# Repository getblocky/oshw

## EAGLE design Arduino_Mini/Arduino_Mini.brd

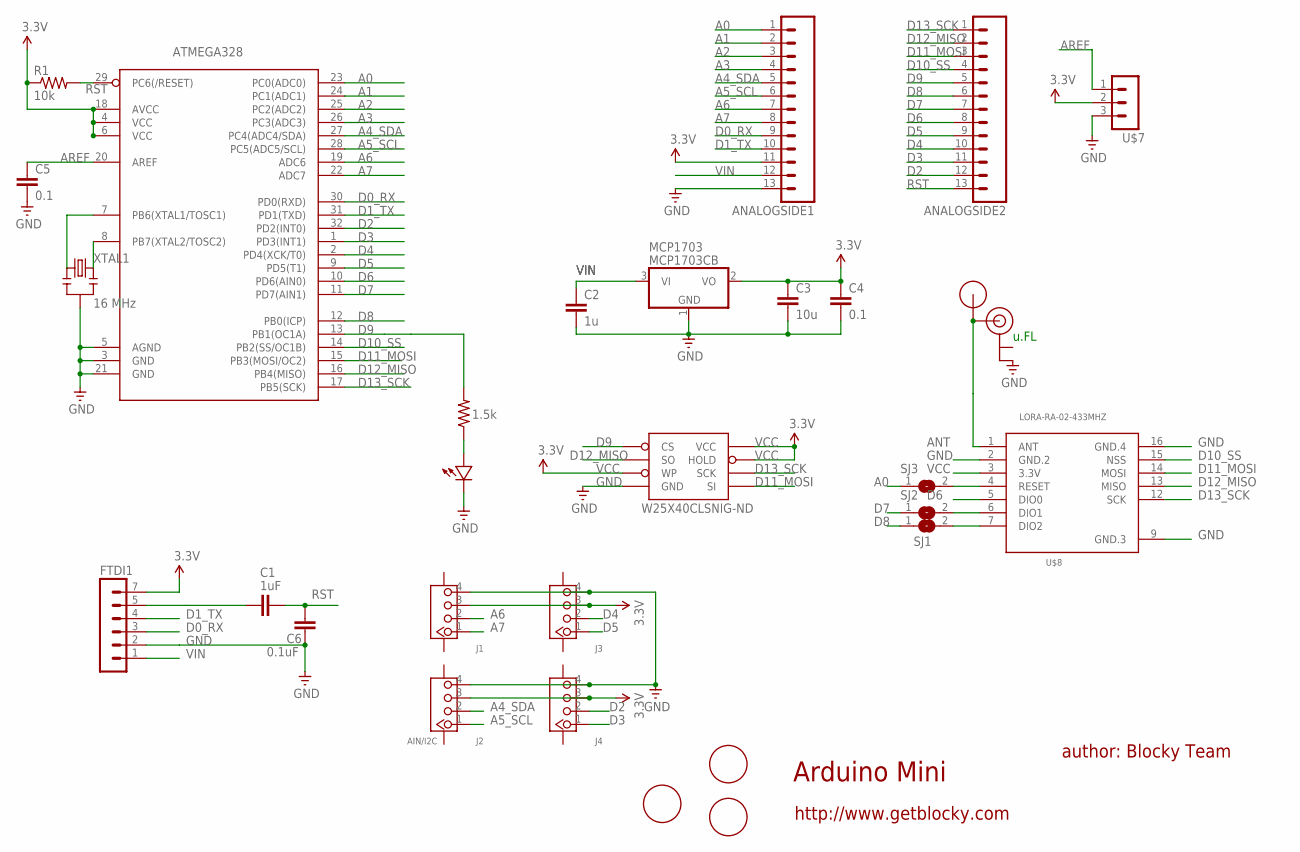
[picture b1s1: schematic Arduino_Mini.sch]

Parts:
ANALOGSIDE1, ANALOGSIDE2: HDR_13PINTHIN_RINGS; 1X13_THINRINGS
ATMEGA328: ATMega-328; TQFP32-08
C1: 1uF; 0603-CAP
C2: 1u; 0603-CAP
C3: 10u; 0805-CAP
C4, C5: 0.1; 0603-CAP
C6: 0.1uF; 0603-CAP
FTDI1: HDR_6PINTHINRINGS; 1X06_NS_THINRINGS
J1, J3, J4: 4P-SMD-2.0-90D; HW4-SMD-2.0-90D
J2: AIN/I2C; HW4-SMD-2.0-90D
LED: LED0603; 0603-LED
MCP1703: MCP1703CB; SOT23
R1: 10k; 0603-RES
R2: 1.5k; 0603-RES
SJ1, SJ2, SJ3: SOLDERJUMPERREFLOW; SOLDERJUMPER_REFLOW
U$1: RFM12B_ANTENNA""; RFM12B-ANTENNA
U$2, U$5, U$6: FIDUCIAL1.5MM; FIDUCIAL_1.5MM
U$4: U.FL
U$7: HDR_3PINTHINRINGS; 1X03_NS_THINRINGS
U$8: LORA-RA-02-433MHZ; LORA-RA2-SMD
W25X40CLSNIG-ND: AT25F512BJEDEC_3.9MM; SO08
XTAL1: 16 MHz; RESONATOR-SMD

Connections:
A0: ANALOGSIDE1.1, ATMEGA328.23 (PC0(ADC0)), SJ3.1
A1: ANALOGSIDE1.2, ATMEGA328.24 (PC1(ADC1))
A2: ANALOGSIDE1.3, ATMEGA328.25 (PC2(ADC2))
A3: ANALOGSIDE1.4, ATMEGA328.26 (PC3(ADC3))
A4_SDA: ANALOGSIDE1.5, ATMEGA328.27 (PC4(ADC4/SDA)), J2.2
A5_SCL: ANALOGSIDE1.6, ATMEGA328.28 (PC5(ADC5/SCL)), J2.1
A6: ANALOGSIDE1.7, ATMEGA328.19 (ADC6), J1.2
A7: ANALOGSIDE1.8, ATMEGA328.22 (ADC7), J1.1
ANT: U$1.P$1, U$4.SIGNAL, U$8.1 (ANT)
AREF: ATMEGA328.20 (AREF), C5.1, U$7.1
D0_RX: ANALOGSIDE1.9, ATMEGA328.30 (PD0(RXD)), FTDI1.3
D1_TX: ANALOGSIDE1.10, ATMEGA328.31 (PD1(TXD)), FTDI1.4
D2: ANALOGSIDE2.12, ATMEGA328.32 (PD2(INT0)), J4.2
D3: ANALOGSIDE2.11, ATMEGA328.1 (PD3(INT1)), J4.1
D4: ANALOGSIDE2.10, ATMEGA328.2 (PD4(XCK/T0)), J3.2
D5: ANALOGSIDE2.9, ATMEGA328.9 (PD5(T1)), J3.1
D6: ANALOGSIDE2.8, ATMEGA328.10 (PD6(AIN0)), U$8.5 (DIO0)
D7: ANALOGSIDE2.7, ATMEGA328.11 (PD7(AIN1)), SJ2.1
D8: ANALOGSIDE2.6, ATMEGA328.12 (PB0(ICP)), SJ1.1
D9: ANALOGSIDE2.5, ATMEGA328.13 (PB1(OC1A)), R2.2, W25X40CLSNIG-ND.1_CS (CS)
D10_SS: ANALOGSIDE2.4, ATMEGA328.14 (PB2(SS/OC1B)), U$8.15 (NSS)
D11_MOSI: ANALOGSIDE2.3, ATMEGA328.15 (PB3(MOSI/OC2)), U$8.14 (MOSI), W25X40CLSNIG-ND.5_SI (SI)
D12_MISO: ANALOGSIDE2.2, ATMEGA328.16 (PB4(MISO)), U$8.13 (MISO), W25X40CLSNIG-ND.2_SO (SO)
D13_SCK: ANALOGSIDE2.1, ATMEGA328.17 (PB5(SCK)), U$8.12 (SCK), W25X40CLSNIG-ND.6_SCK (SCK)
DIO1: SJ2.2, U$8.6 (DIO1)
DIO2: SJ1.2, U$8.7 (DIO2)
GND: ANALOGSIDE1.13, ATMEGA328.3 (GND), ATMEGA328.5 (AGND), ATMEGA328.21 (GND), C2.2, C3.2, C4.2, C5.2, C6.2, FTDI1.2, J1.4, J2.4, J3.4, J4.4, LED.MINUS, MCP1703.1 (GND), U$4.GND2 (GND), U$7.3, U$8.2 (GND.2), U$8.9 (GND.3), U$8.16 (GND.4), W25X40CLSNIG-ND.4_GND (GND), XTAL1.2
unnamed: ATMEGA328.7 (PB6(XTAL1/TOSC1)), XTAL1.1
unnamed: LED.PLUS, R2.1
unnamed: SJ3.2, U$8.4 (RESET)
unnamed: C1.2, FTDI1.5
unnamed: ATMEGA328.8 (PB7(XTAL2/TOSC2)), XTAL1.3
RST: ANALOGSIDE2.13, ATMEGA328.29 (PC6(/RESET)), C1.1, C6.1, R1.2
VCC: ANALOGSIDE1.11, ATMEGA328.4 (VCC), ATMEGA328.6 (VCC), ATMEGA328.18 (AVCC), C3.1, C4.1, FTDI1.7 (6), J1.3, J2.3, J3.3, J4.3, MCP1703.2 (VO), R1.1, U$7.2, U$8.3 (3.3V), W25X40CLSNIG-ND.3_WP (WP), W25X40CLSNIG-ND.7_HOLD (HOLD), W25X40CLSNIG-ND.8_VCC (VCC)
VIN: ANALOGSIDE1.12, C2.1, FTDI1.1, MCP1703.3 (VI)

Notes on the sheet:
Arduino Mini
author: Blocky Team
http://www.getblocky.com
u.FL

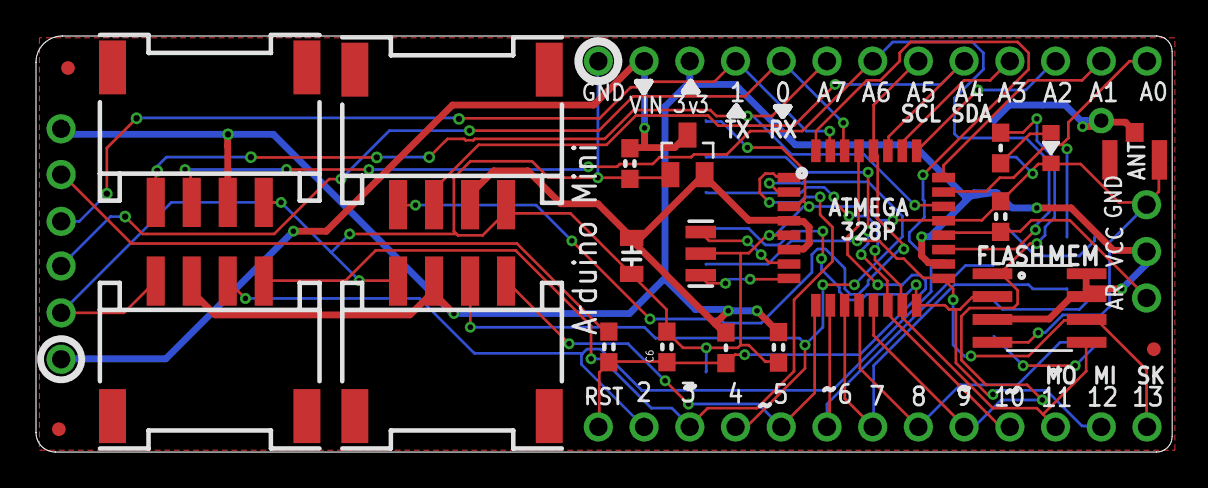
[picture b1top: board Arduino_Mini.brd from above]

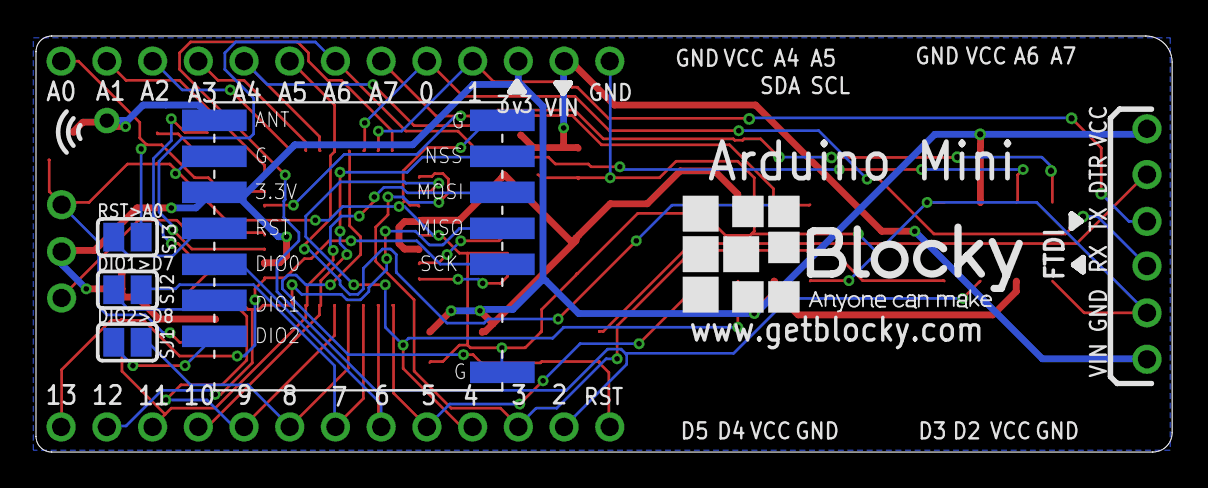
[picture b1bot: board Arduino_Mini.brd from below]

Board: 2 copper layers, 63.1 x 23.1 mm, 31 parts (5 on the bottom side), 35 nets.

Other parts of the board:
U$3: BLOCKY_LOGO

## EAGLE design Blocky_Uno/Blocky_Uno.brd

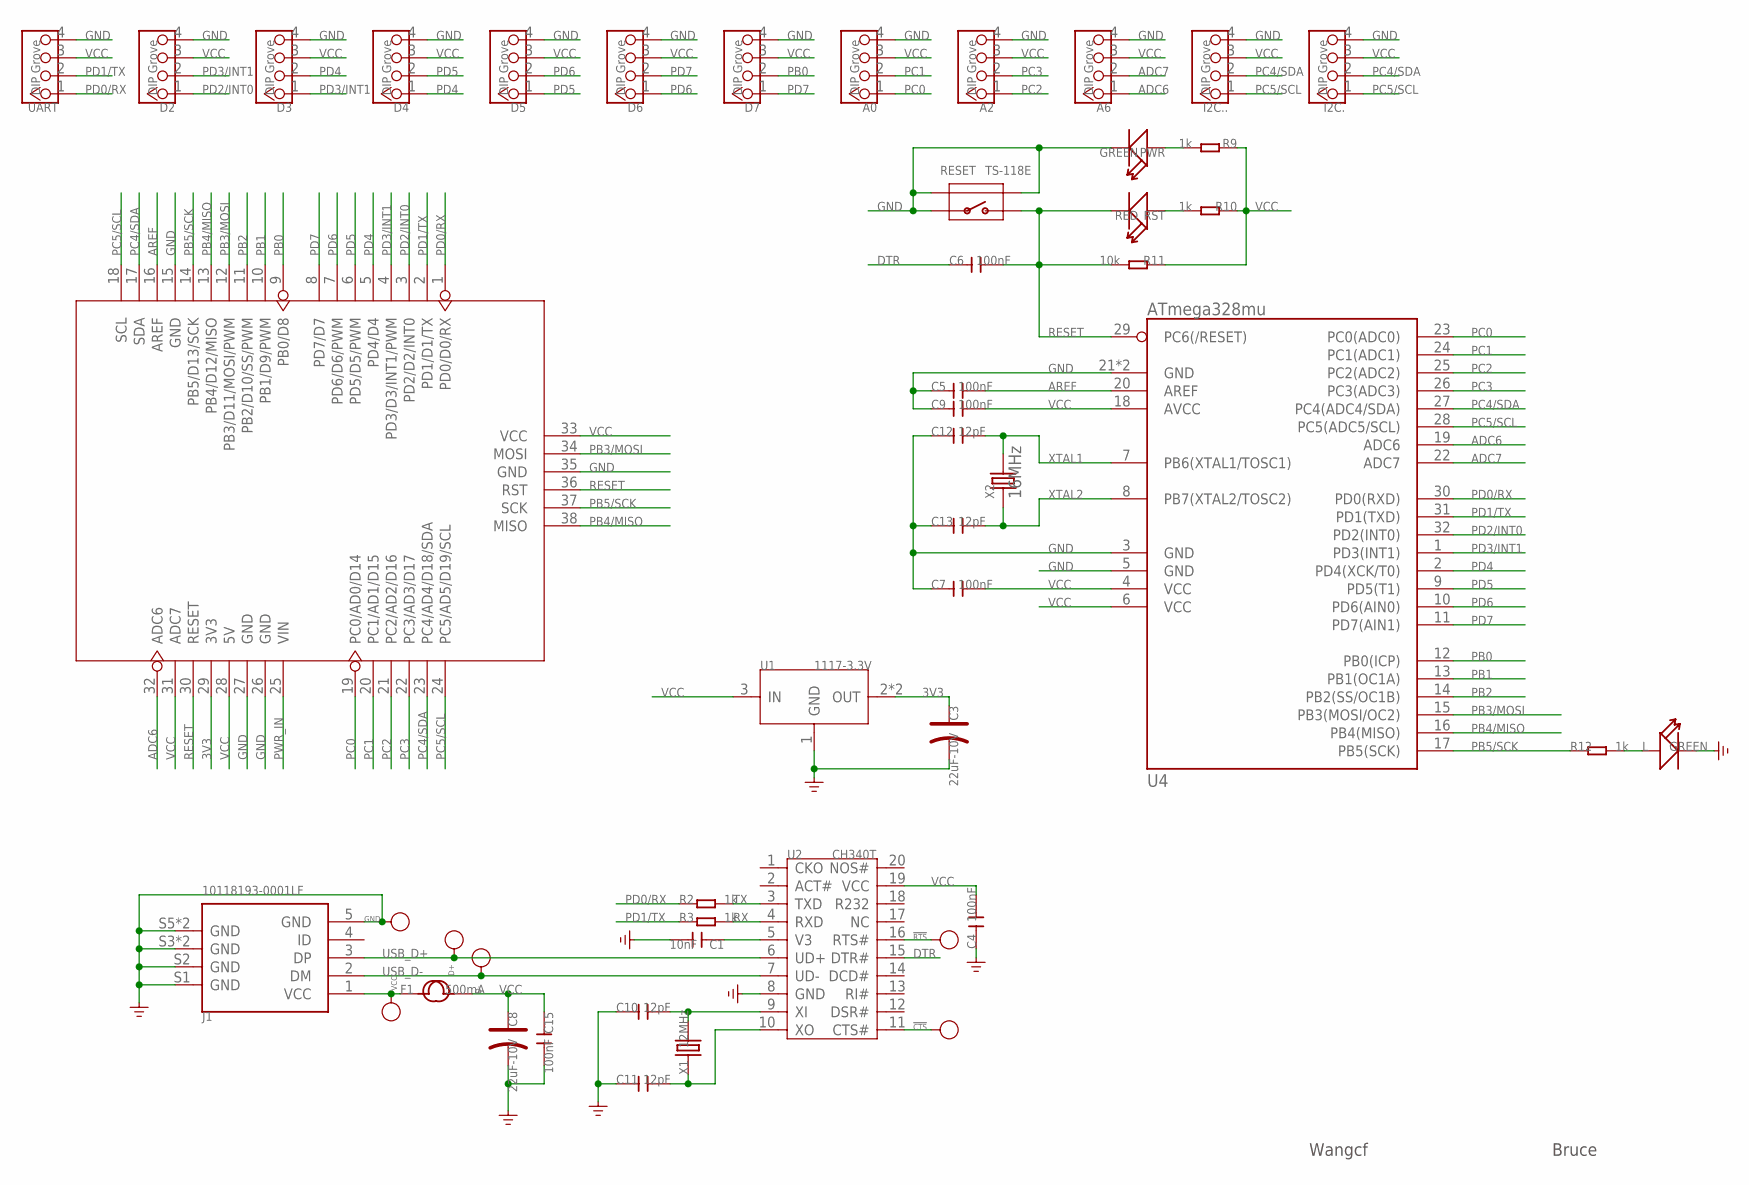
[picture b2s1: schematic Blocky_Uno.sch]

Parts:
!CTS: PAD-TEST-POINT'4545'; TP_4545
!RTS: PAD-TEST-POINT'4545'; TP_4545
A0, A2, A6: DIP Grove; 4P-2.0
C1: 10nF; C0603
C3, C8: 22uF-10V; AVX-A
C4, C5, C6, C7, C9, C15: 100nF; C0603
C10, C11, C12, C13: 12pF; C0603
D2, D3, D4, D5, D6, D7: DIP Grove; 4P-2.0
D+: PAD-TEST-POINT'4545'; TP_4545
D-: PAD-TEST-POINT'4545'; TP_4545
F1: 500mA; F1206
GND: PAD-TEST-POINT'4545'; TP_4545
I2C., I2C..: DIP Grove; 4P-2.0
J1: 10118193-0001LF; MICRO-USB5+6P-SMD-0.65-B
L: GREEN; LED-0603
PWR: GREEN; LED-0603
R2, R3, R9, R10, R12: 1k; R0603
R11: 10k; R0603
RESET: TS-118E; 4P-SMD-7X3.5X3.5H
RST: RED; LED-0603
U1: 1117-3.3V; SOT89
U2: CH340T; SSOP20
U3: ARDUINO-38P
U4: ATmega328mu; MLF32X-W/HEAT
UART: DIP Grove; 4P-2.0
VCC: PAD-TEST-POINT'4545'; TP_4545
X1: 12MHz; 2P-SMD-5X3.2
X2: 16MHz; 2P-SMD-5X3.2

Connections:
3V3: C3.+, U1.2 (OUT), U1.4 (OUT), U3.29 (3V3)
ADC6: A6.1, U3.32 (ADC6), U4.19 (ADC6)
ADC7: A6.2, U4.22 (ADC7)
AREF: C5.2, U3.16 (AREF), U4.20 (AREF)
CTS: !CTS.T, U2.11 (CTS#)
DTR: C6.1, U2.15 (DTR#)
GND: A0.4, A2.4, A6.4, C1.2, C3.-, C4.1, C5.1, C7.1, C8.-, C9.1, C10.1, C11.1, C12.1, C13.1, C15.2, D2.4, D3.4, D4.4, D5.4, D6.4, D7.4, GND.T, I2C..4, I2C...4, J1.5 (GND), J1.S1 (GND), J1.S2 (GND), J1.S3 (GND), J1.S4 (GND), J1.S5 (GND), J1.S6 (GND), L.-, PWR.-, RESET.1, RESET.S1, RESET.S2, U1.1 (GND), U2.8 (GND), U3.15 (GND), U3.26 (GND), U3.27 (GND), U3.35 (GND), U4.3 (GND), U4.5 (GND), U4.21 (GND), U4.HEAT (GND), UART.4
unnamed: R10.2, RST.+
unnamed: PWR.+, R9.2
unnamed: C10.2, U2.9 (XI), X1.2
unnamed: C11.2, U2.10 (XO), X1.1
unnamed: !RTS.T, U2.16 (RTS#)
unnamed: F1.1, J1.1 (VCC), VCC.T
unnamed: L.+, R12.2
PB0: D7.2, U3.9 (PB0/D8), U4.12 (PB0(ICP))
PB1: U3.10 (PB1/D9/PWM), U4.13 (PB1(OC1A))
PB2: U3.11 (PB2/D10/SS/PWM), U4.14 (PB2(SS/OC1B))
PB3/MOSI: U3.12 (PB3/D11/MOSI/PWM), U3.34 (MOSI), U4.15 (PB3(MOSI/OC2))
PB4/MISO: U3.13 (PB4/D12/MISO), U3.38 (MISO), U4.16 (PB4(MISO))
PB5/SCK: R12.1, U3.14 (PB5/D13/SCK), U3.37 (SCK), U4.17 (PB5(SCK))
PC0: A0.1, U3.19 (PC0/AD0/D14), U4.23 (PC0(ADC0))
PC1: A0.2, U3.20 (PC1/AD1/D15), U4.24 (PC1(ADC1))
PC2: A2.1, U3.21 (PC2/AD2/D16), U4.25 (PC2(ADC2))
PC3: A2.2, U3.22 (PC3/AD3/D17), U4.26 (PC3(ADC3))
PC4/SDA: I2C..2, I2C...2, U3.17 (SDA), U3.23 (PC4/AD4/D18/SDA), U4.27 (PC4(ADC4/SDA))
PC5/SCL: I2C..1, I2C...1, U3.18 (SCL), U3.24 (PC5/AD5/D19/SCL), U4.28 (PC5(ADC5/SCL))
PD0/RX: R2.1, U3.1 (PD0/D0/RX), U4.30 (PD0(RXD)), UART.1
PD1/TX: R3.1, U3.2 (PD1/D1/TX), U4.31 (PD1(TXD)), UART.2
PD2/INT0: D2.1, U3.3 (PD2/D2/INT0), U4.32 (PD2(INT0))
PD3/INT1: D2.2, D3.1, U3.4 (PD3/D3/INT1/PWM), U4.1 (PD3(INT1))
PD4: D3.2, D4.1, U3.5 (PD4/D4), U4.2 (PD4(XCK/T0))
PD5: D4.2, D5.1, U3.6 (PD5/D5/PWM), U4.9 (PD5(T1))
PD6: D5.2, D6.1, U3.7 (PD6/D6/PWM), U4.10 (PD6(AIN0))
PD7: D6.2, D7.1, U3.8 (PD7/D7), U4.11 (PD7(AIN1))
PWR_IN: U3.25 (VIN)
RESET: C6.2, R11.2, RESET.2, RST.-, U3.30 (RESET), U3.36 (RST), U4.29 (PC6(/RESET))
RX: R3.2, U2.4 (RXD)
TX: R2.2, U2.3 (TXD)
USB_D+: D+.T, J1.3 (DP), U2.6 (UD+)
USB_D-: D-.T, J1.2 (DM), U2.7 (UD-)
V3: C1.1, U2.5 (V3)
VCC: A0.3, A2.3, A6.3, C4.2, C7.2, C8.+, C9.2, C15.1, D2.3, D3.3, D4.3, D5.3, D6.3, D7.3, F1.2, I2C..3, I2C...3, R9.1, R10.1, R11.1, U1.3 (IN), U2.19 (VCC), U3.28 (5V), U3.31 (ADC7), U3.33 (VCC), U4.4 (VCC), U4.6 (VCC), U4.18 (AVCC), UART.3
XTAL1: C12.2, U4.7 (PB6(XTAL1/TOSC1)), X2.2
XTAL2: C13.2, U4.8 (PB7(XTAL2/TOSC2)), X2.1

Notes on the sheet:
Wangcf
Bruce

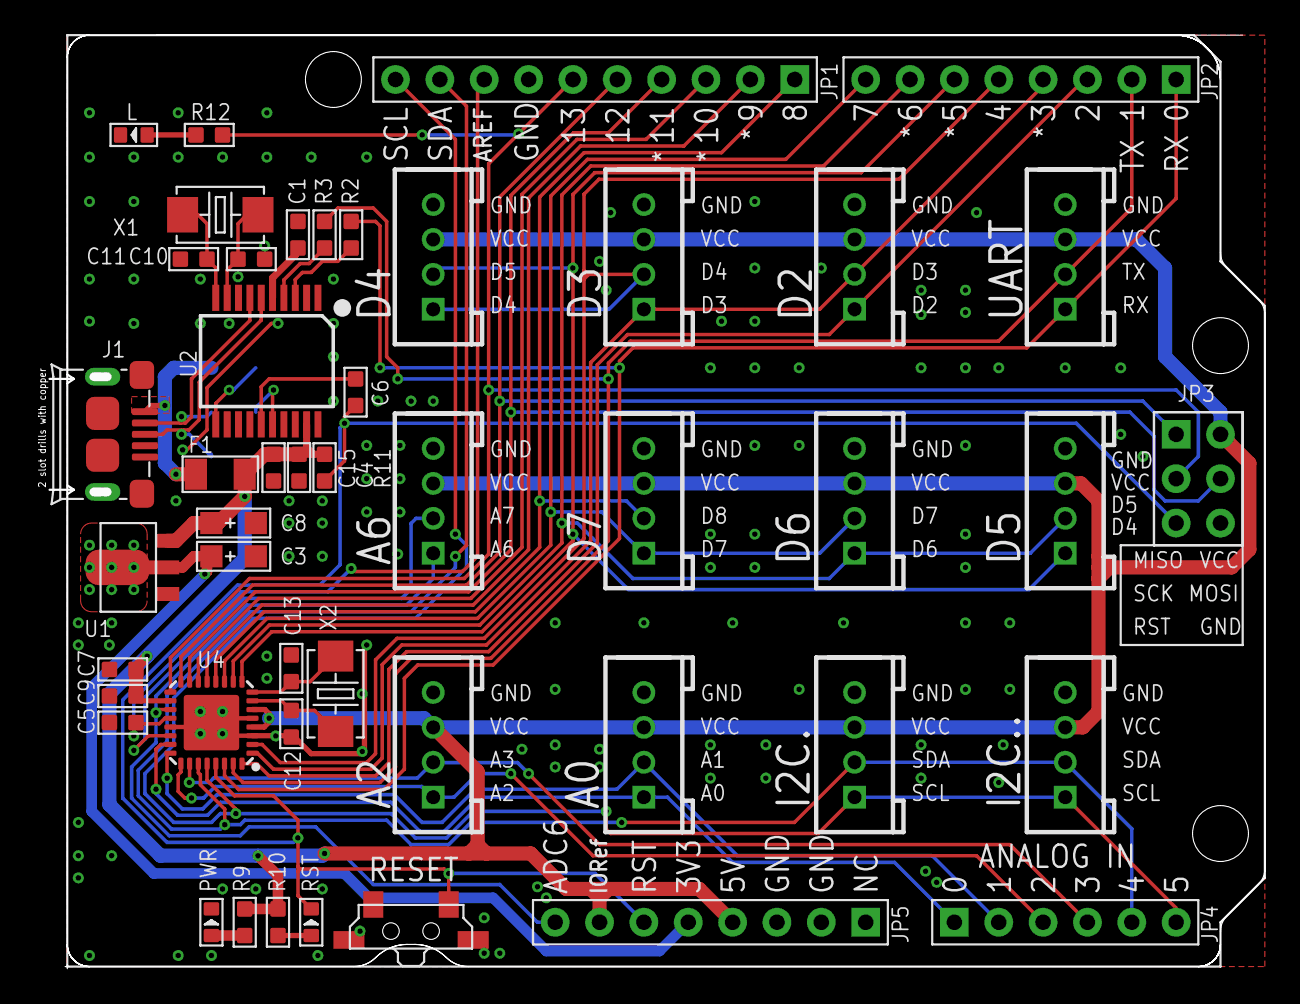
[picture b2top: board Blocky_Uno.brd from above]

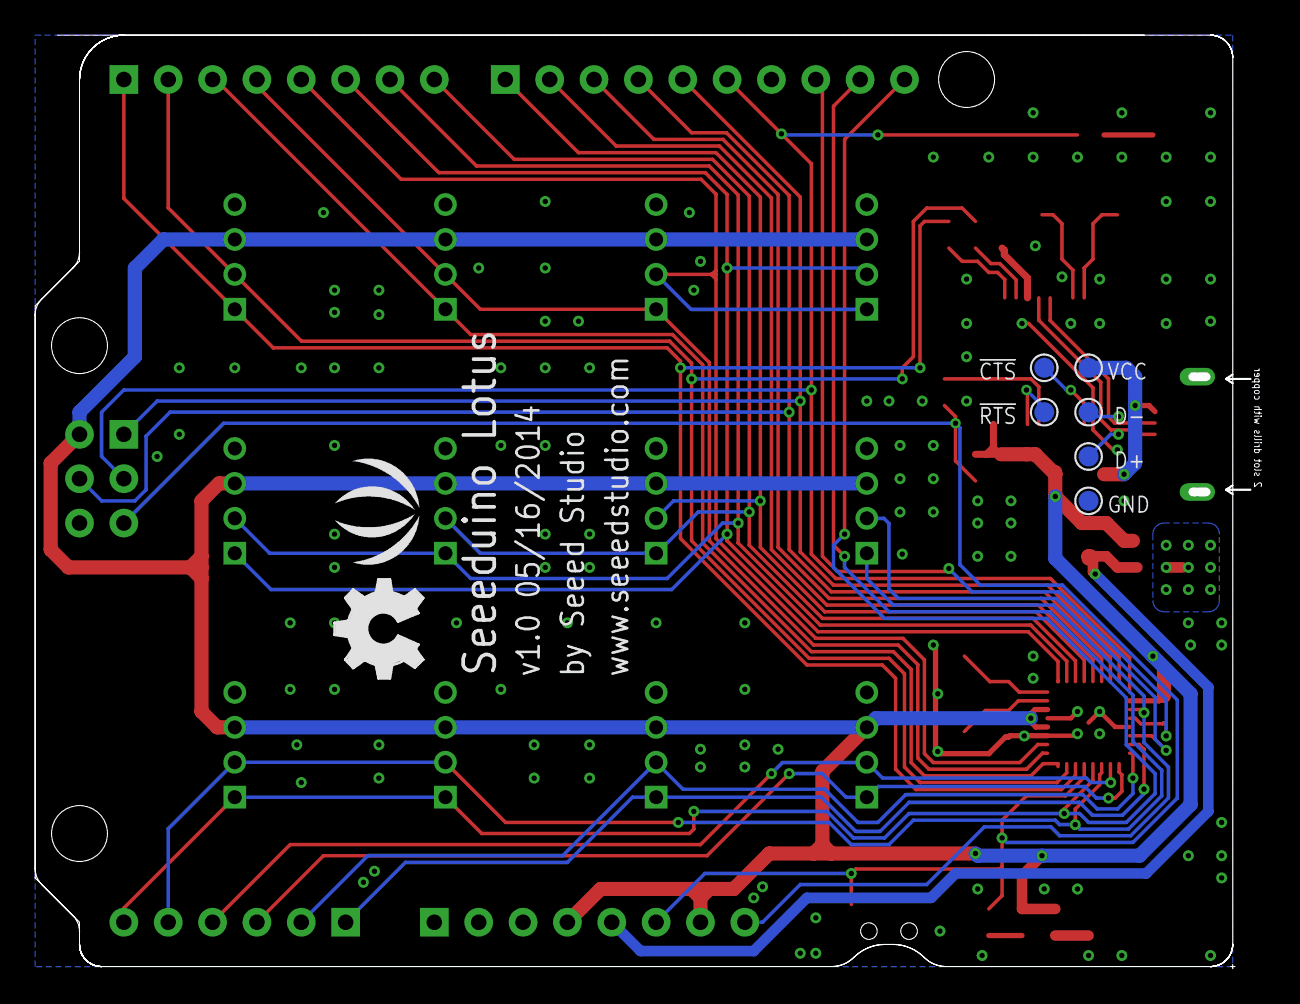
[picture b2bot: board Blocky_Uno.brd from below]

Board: 2 copper layers, 69.6 x 53.5 mm, 52 parts (8 on the bottom side), 43 nets.

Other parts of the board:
U$2: OSHW_FILLX200_NOTEXT
U$4: LOGO_SILK
U$12: SEEED_MASK

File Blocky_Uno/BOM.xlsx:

| Part | Package | Quantity | Link
 | DIP Grove | 4P-2.0 | 12
 | 10nF | C0603 | 1
 | Cap tantalum 3216 22uF 10V | AVX-A 3216 | 2 | https://www.aliexpress.com/item/Free-shipping-20pcs-A-3216-2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
 | 100nF | C0603 | 6
 | 12pF | C0603 | 4
 | Fuse 1206 500mA | F1206 | 1 | https://www.aliexpress.com/item/100PCS-1206-0-5A-0-5-Amp-500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
 | MICRO-B-SMD 10118193-0001LF | MICRO-USB | 1 | https://www.digikey.com/product-detail/en/amphenol-fci/10118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
 | LED GREEN | LED-0603 | 2
 | Resistor 1k | R0603 | 5
 | Resistor 10k | R0603 | 1
 | Side SMD Tact Switch 3.5x7.0x3.5 TS-118E | 4P-SMD-7X3.5X3.5H | 1 | https://www.aliexpress.com/item/1000pcs-on-tape-reel-Horizon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
 | LED RED | LED-0603 | 1
 | LDO AMS1117-3.3V SOT89 | SOT89 | 1 | https://www.aliexpress.com/item/100PCS-AMS1117-3-3V-AMS1117-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
 | CH340T | SSOP20 | 1 | https://www.aliexpress.com/item/Smd-CH340T-wch-usb-to-serial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
 | Atmega328p-mu | MLF32X-W/HEAT | 1 | https://www.aliexpress.com/item/Free-Shipping-ATMEGA328P-MUR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
 | Crystal SMD 5032 12MHz | 2P-SMD-5X3.2 | 1 | https://www.aliexpress.com/item/NDK-NX5032GA-NX5032GB-12M-12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
 | Crystal SMD 5032 16MHz | 2P-SMD-5X3.2 | 1 | Crystal SMD 16MHz 5032 https://www.aliexpress.com/item/20PCS-16MHZ-5032-SMD-Pas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

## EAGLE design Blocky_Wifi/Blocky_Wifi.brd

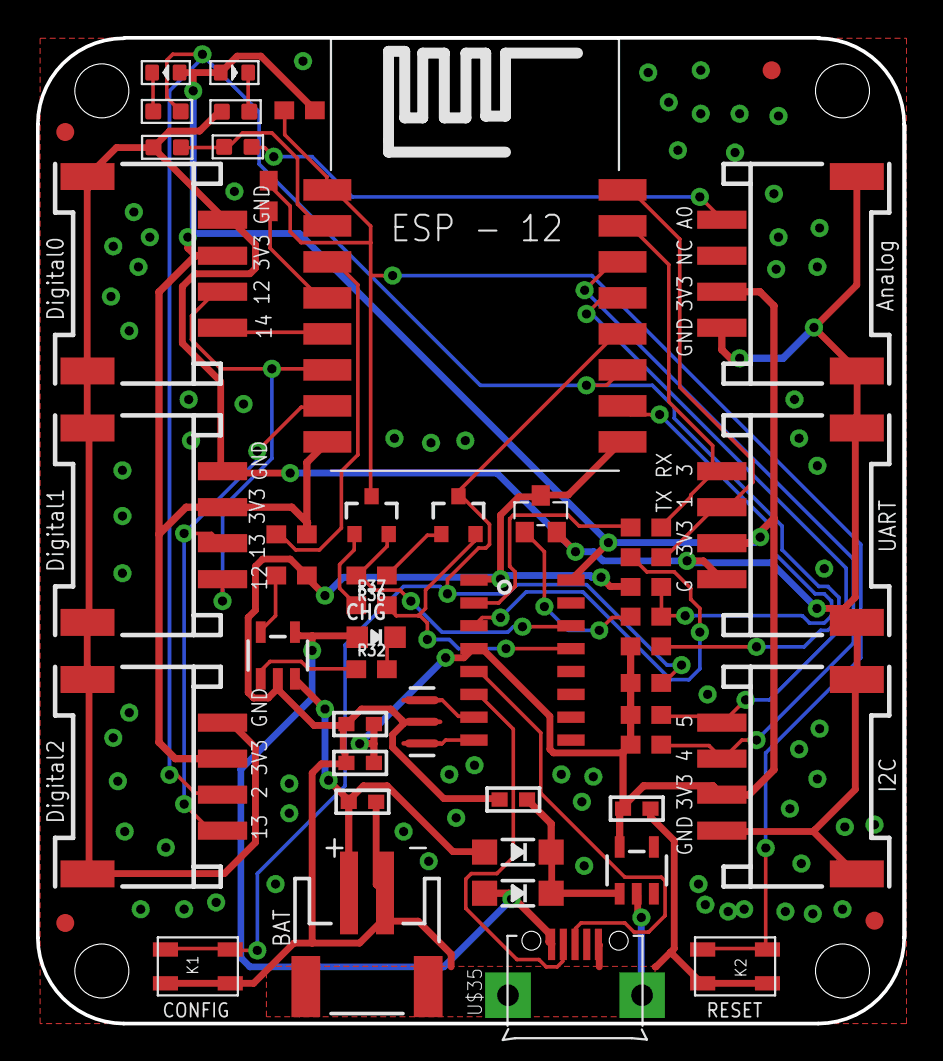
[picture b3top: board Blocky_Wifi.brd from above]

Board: 2 copper layers, 48.1 x 54.8 mm, 52 parts (1 on the bottom side), 37 nets.

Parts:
C1: 1uF; _0603
C3, C6, C10: 10uF; _0603
C11: 0.1uF; _0603
CHG: CHARGE; CHIPLED_0805_NOOUTLINE
D4: Blue; LED-0603
D5: Red; LED-0603
D6, D7: MBR120; SOD-123
J3, J4, J5, J6, J7, J8: DIP Grove; HW4-SMD-2.0-90D
J9: JST-2-SMD
K1, K2: button 311020045; SW4P-SMD-4.5X3.2X2.5MM
Q3, Q6: S8050; SOT23-3
Q7: S8050; SOT-23
R1, R2, R3, R4, R5, R7, R27, R36, R37: 10K; 0603
R6: 100K; 0603
R15, R32: 1K; 0603
R21, R22: 1k; R0603
R25: 220k; R0603
R26: 100k; R0603
R33: 2K; 0603
R34, R35: 330; 0603
U1: ESP-12F; ESP12-SMD
U2: SPX3819; SOT23-5
U4: MCP73831; SOT23-5
U$9, U$10, U$11, U$12: FIDUCIAL; FIDUCIAL_1MM
U$15: BLOCKY_LOGO
U$35: MICRO-USB
U$44: CH340G; SOIC16
Y1: 12Mhz; RESONATOR-SMD-3.2X1.3

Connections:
3.3V: C1.1, C10.1, C11.1, D4.+, D5.+, J3.3, J4.3, J5.3, J6.3, J7.3, J8.3, R1.2, R2.2, R3.1, R4.2, R5.1, R7.2, U1.VCC, U2.5, U$44.4, U$44.16
ADC: R25.1, R26.2, U1.ADC
CH_PD: R4.1, U1.CH_PD
D+: U$35.3, U$44.5
D-: U$35.2, U$44.6
DTR: Q6.2, R37.2, U$44.13
GND: C1.2, C3.2, C6.2, C10.2, C11.2, J9.1, K1.1, K1.2, K2.1, K2.2, Q7.3, R27.1, R33.1, U1.GND, U2.2, U4.2, U$35.5, U$35.GND1, U$35.GND2, U$44.1, Y1.2
GND_SW: J3.4, J3.SS1, J3.SS2, J4.4, J4.SS1, J4.SS2, J5.4, J5.SS1, J5.SS2, J6.4, J6.SS1, J6.SS2, J7.4, J7.SS1, J7.SS2, J8.4, J8.SS1, J8.SS2, Q7.2, R22.2, R26.1
GPIO0: K1.3, K1.4, Q6.3, R2.1, U1.GPIO0
GPIO2: J5.2, R7.1, R21.2, U1.GPIO2
GPIO4: J8.2, R5.2, U1.GPIO4
GPIO5: J8.1, R3.2, U1.GPIO5
GPIO12: J4.2, J7.1, U1.GPIO12
GPIO13: J5.1, J7.2, U1.GPIO13
GPIO14: J4.1, U1.GPIO14
GPIO15: R15.2, R27.2, U1.GPIO15
GPIO16: R6.2, U1.GPIO16
unnamed: CHG.C, R32.2
unnamed: Q3.1, R37.1
unnamed: Q6.1, R36.1
unnamed: U$44.7, Y1.1
unnamed: J6.1, R25.2
unnamed: U$44.8, Y1.3
unnamed: D4.-, R21.1
unnamed: R34.1, U$44.2
unnamed: D5.-, R22.1
unnamed: R35.1, U$44.3
unnamed: Q7.1, R15.1
POW: C6.1, D6.C, D7.C, U2.1
PROG: R33.2, U4.5
RST: K2.3, K2.4, Q3.3, R1.1, R6.1, U1.RESET
RTS: Q3.2, R36.2, U$44.14
RX: J3.1, R34.2, U1.RXD0
STAT: R32.1, U4.1
TX: J3.2, R35.2, U1.TXD0
VBAT: C3.1, D6.A, J9.2, U4.3
VBUS: CHG.A, D7.A, U4.4, U$35.1

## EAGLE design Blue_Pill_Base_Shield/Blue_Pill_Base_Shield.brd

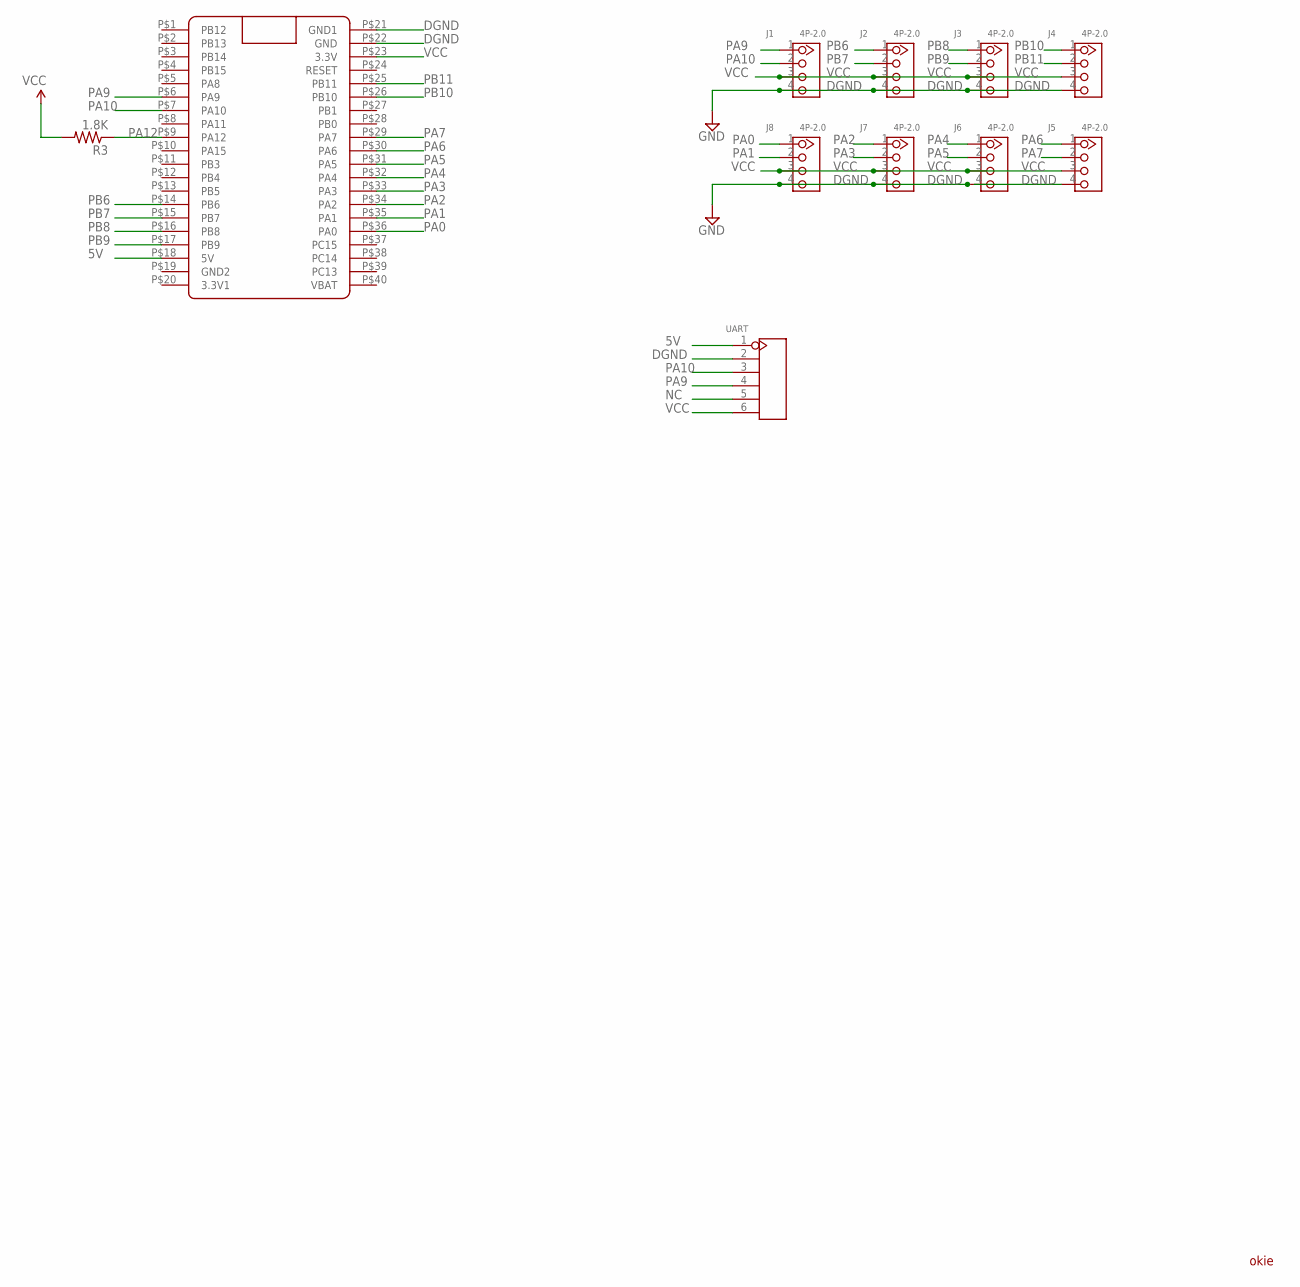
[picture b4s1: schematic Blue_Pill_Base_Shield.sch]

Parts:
J1, J2, J3, J4, J5, J6, J7, J8: 4P-2.0; HW4-2.0
R3: 1.8K; 0603
U$5: BLUE_PILL
UART: YELLOW-6P-2.54; H6-2.54

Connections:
5V: U$5.P$18 (5V), UART.1
DGND: J1.4, J2.4, J3.4, J4.4, J5.4, J6.4, J7.4, J8.4, U$5.P$21 (GND1), U$5.P$22 (GND), UART.2
NC: UART.5
PA0: J8.1, U$5.P$36 (PA0)
PA1: J8.2, U$5.P$35 (PA1)
PA2: J7.1, U$5.P$34 (PA2)
PA3: J7.2, U$5.P$33 (PA3)
PA4: J6.1, U$5.P$32 (PA4)
PA5: J6.2, U$5.P$31 (PA5)
PA6: J5.1, U$5.P$30 (PA6)
PA7: J5.2, U$5.P$29 (PA7)
PA9: J1.1, U$5.P$6 (PA9), UART.4
PA10: J1.2, U$5.P$7 (PA10), UART.3
PA12: R3.1, U$5.P$9 (PA12)
PB6: J2.1, U$5.P$14 (PB6)
PB7: J2.2, U$5.P$15 (PB7)
PB8: J3.1, U$5.P$16 (PB8)
PB9: J3.2, U$5.P$17 (PB9)
PB10: J4.1, U$5.P$26 (PB10)
PB11: J4.2, U$5.P$25 (PB11)
VCC: J1.3, J2.3, J3.3, J4.3, J5.3, J6.3, J7.3, J8.3, R3.2, U$5.P$23 (3.3V), UART.6

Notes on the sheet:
okie

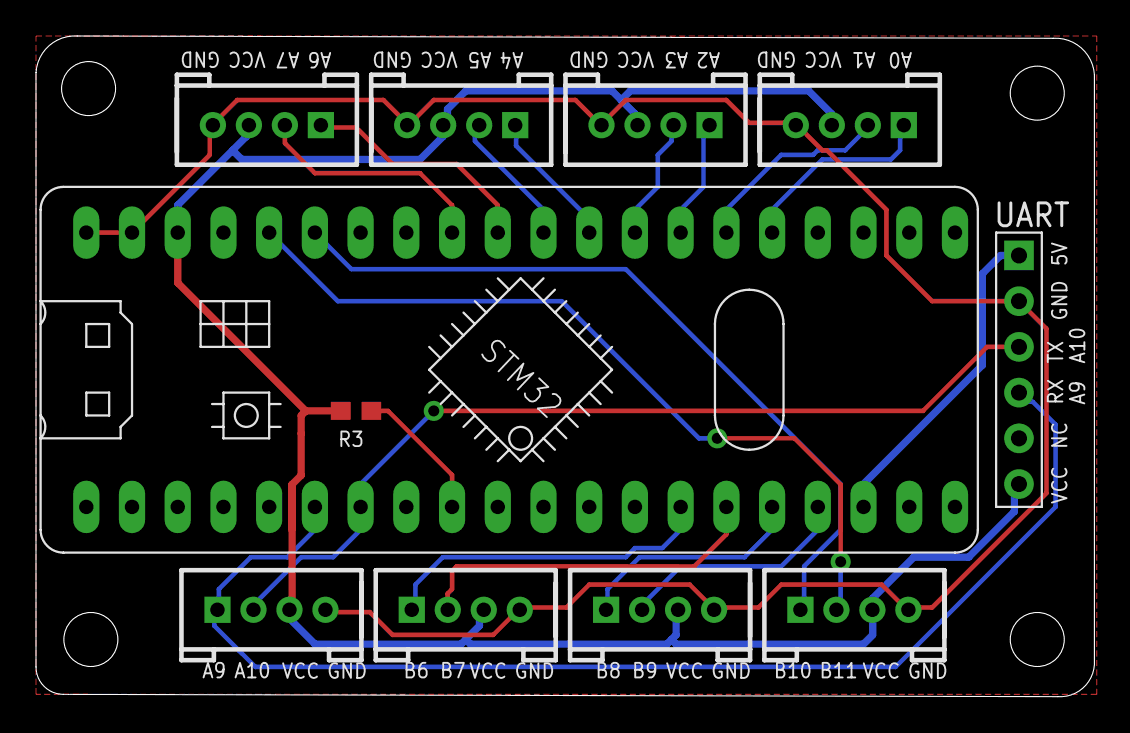
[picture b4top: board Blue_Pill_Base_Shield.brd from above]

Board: 2 copper layers, 58.8 x 36.7 mm, 16 parts (1 on the bottom side), 20 nets.

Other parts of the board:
U$1, U$2, U$3, U$4: KFH-M3
U$6: BLOCKY_LOGO

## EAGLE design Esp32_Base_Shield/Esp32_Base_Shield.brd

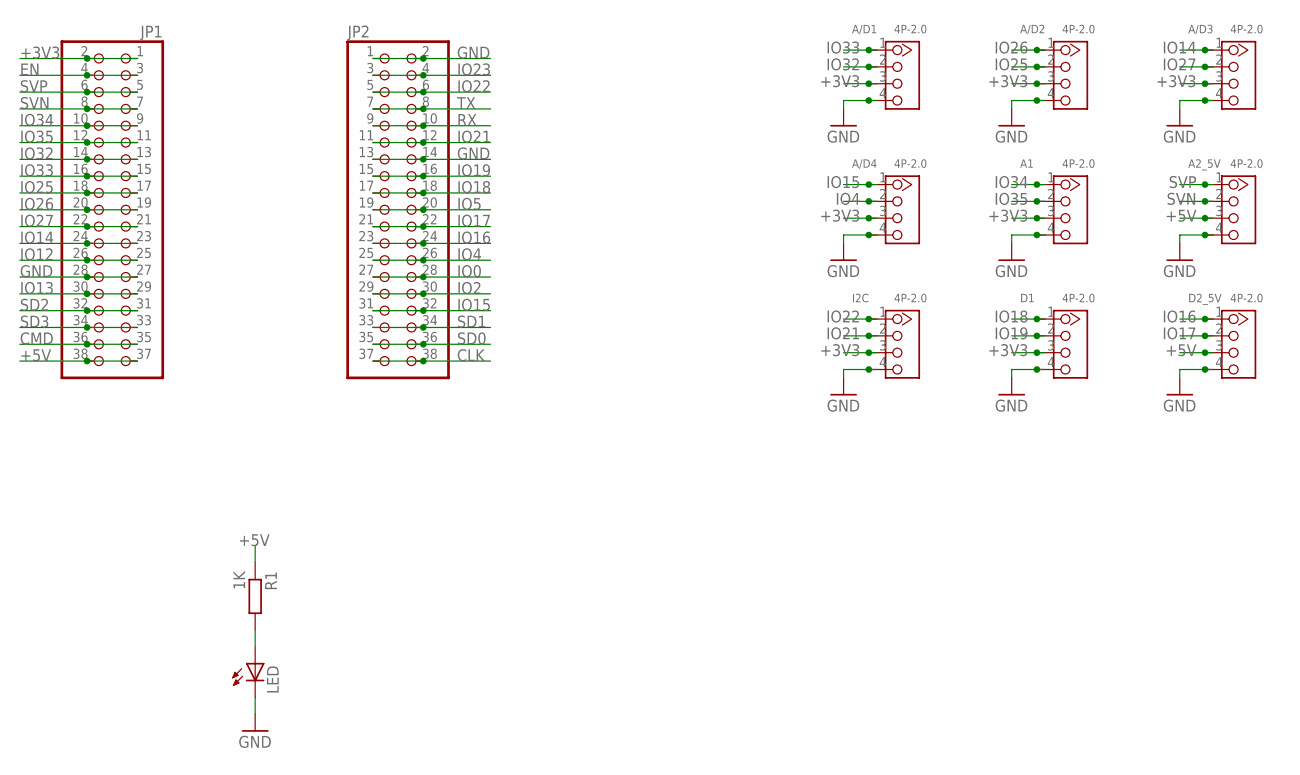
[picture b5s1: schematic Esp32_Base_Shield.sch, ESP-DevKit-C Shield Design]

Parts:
A1, A2_5V: 4P-2.0; HW4-2.0
A/D1, A/D2, A/D3, A/D4: 4P-2.0; HW4-2.0
D1, D2_5V: 4P-2.0; HW4-2.0
I2C: 4P-2.0; HW4-2.0
JP1, JP2: PINHD-2X19; 2X19
LED: LED3MM
R1: 1K; 0207/10

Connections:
+3V3: A1.3, A/D1.3, A/D2.3, A/D3.3, A/D4.3, D1.3, I2C.3, JP1.1, JP1.2
+5V: A2_5V.3, D2_5V.3, JP1.37, JP1.38, R1.1
CLK: JP2.37, JP2.38
CMD: JP1.35, JP1.36
CRC: LED.A, R1.2
EN: JP1.3, JP1.4
GND: A1.4, A2_5V.4, A/D1.4, A/D2.4, A/D3.4, A/D4.4, D1.4, D2_5V.4, I2C.4, JP1.27, JP1.28, JP2.1, JP2.2, JP2.13, JP2.14, LED.K (C)
IO0: JP2.27, JP2.28
IO2: JP2.29, JP2.30
IO4: A/D4.2, JP2.25, JP2.26
IO5: JP2.19, JP2.20
IO12: JP1.25, JP1.26
IO13: JP1.29, JP1.30
IO14: A/D3.1, JP1.23, JP1.24
IO15: A/D4.1, JP2.31, JP2.32
IO16: D2_5V.1, JP2.23, JP2.24
IO17: D2_5V.2, JP2.21, JP2.22
IO18: D1.1, JP2.17, JP2.18
IO19: D1.2, JP2.15, JP2.16
IO21: I2C.2, JP2.11, JP2.12
IO22: I2C.1, JP2.5, JP2.6
IO23: JP2.3, JP2.4
IO25: A/D2.2, JP1.17, JP1.18
IO26: A/D2.1, JP1.19, JP1.20
IO27: A/D3.2, JP1.21, JP1.22
IO32: A/D1.2, JP1.13, JP1.14
IO33: A/D1.1, JP1.15, JP1.16
IO34: A1.1, JP1.9, JP1.10
IO35: A1.2, JP1.11, JP1.12
RX: JP2.9, JP2.10
SD0: JP2.35, JP2.36
SD1: JP2.33, JP2.34
SD2: JP1.31, JP1.32
SD3: JP1.33, JP1.34
SVN: A2_5V.2, JP1.7, JP1.8
SVP: A2_5V.1, JP1.5, JP1.6
TX: JP2.7, JP2.8

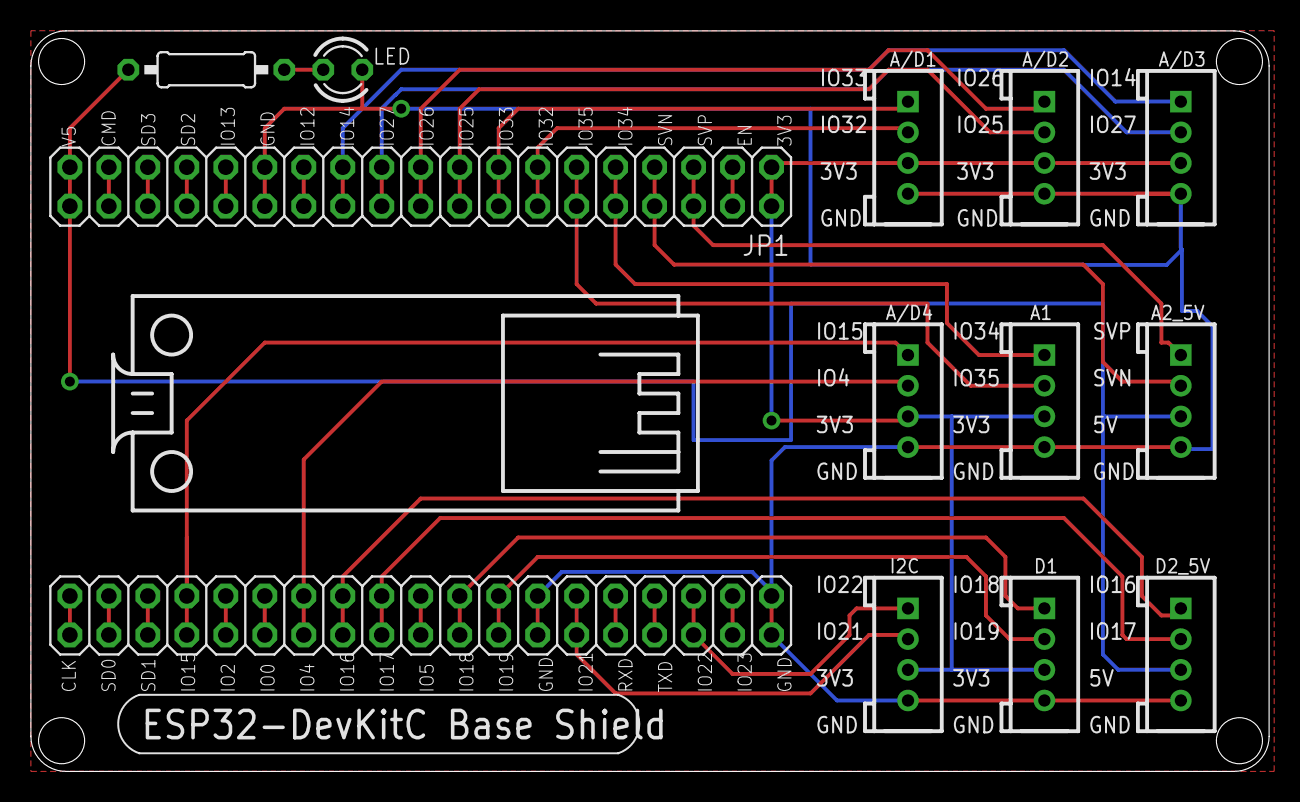
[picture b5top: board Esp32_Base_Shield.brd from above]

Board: 2 copper layers, 80.7 x 48.2 mm, 15 parts (1 on the bottom side), 37 nets.

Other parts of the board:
U$1: BLOCKY_LOGO
U$5: BREADBOARD_SPACING

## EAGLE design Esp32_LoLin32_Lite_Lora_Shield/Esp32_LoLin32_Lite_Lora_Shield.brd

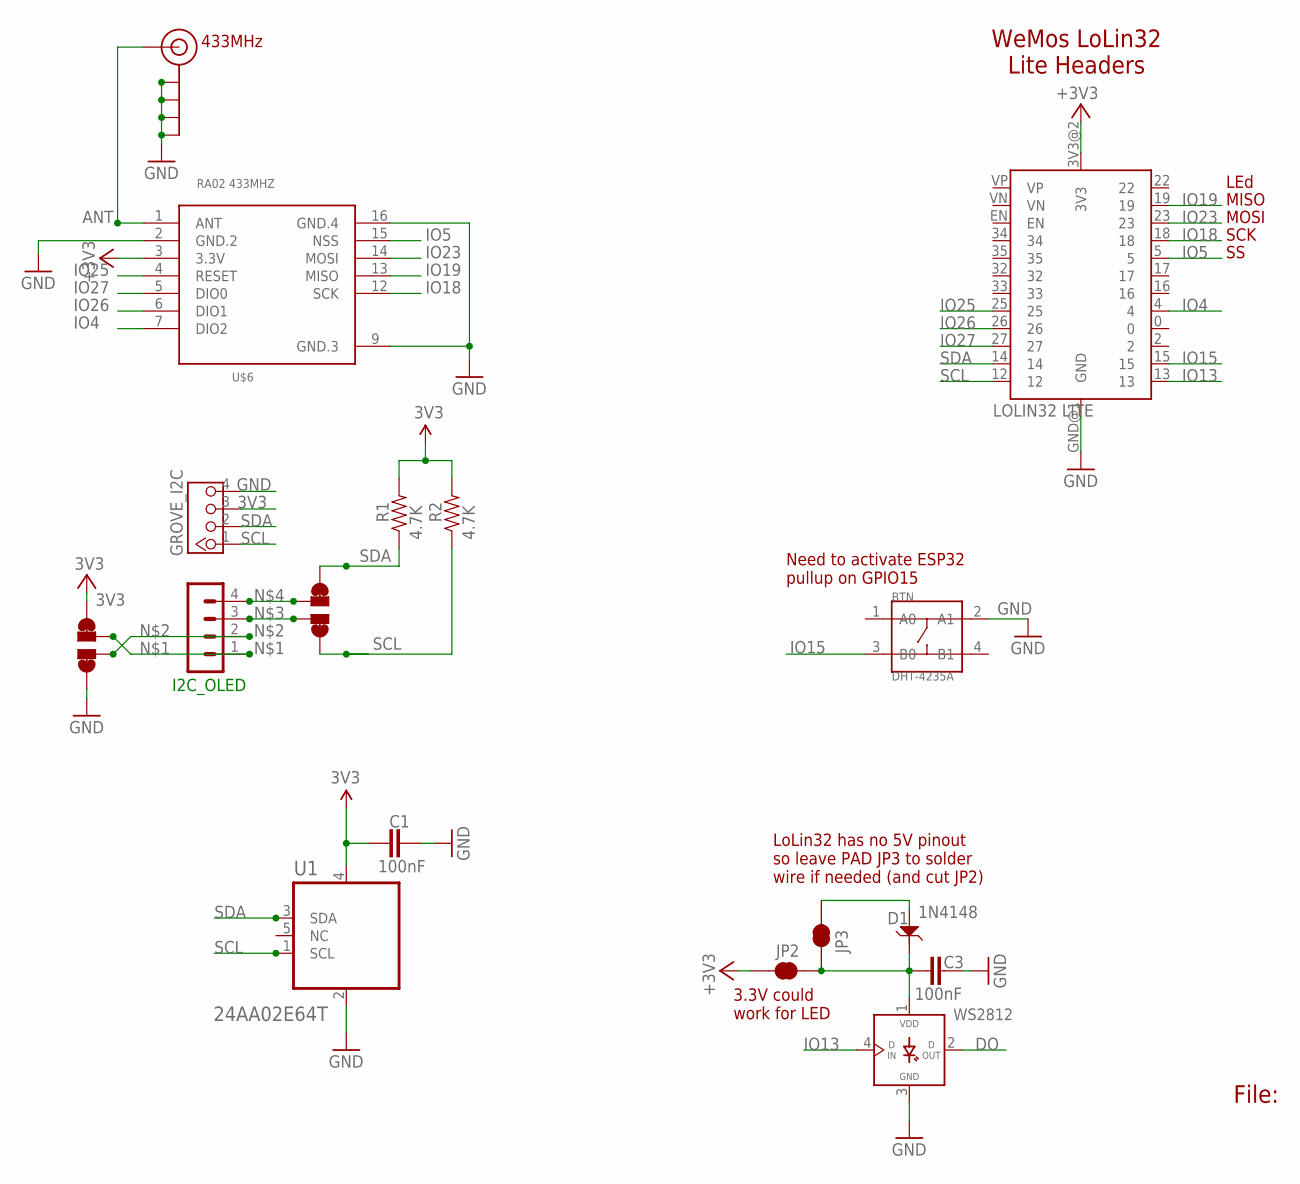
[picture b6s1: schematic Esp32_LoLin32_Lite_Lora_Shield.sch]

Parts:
BTN: DHT-4235A; SW4-SMD-4.2X3.2X2.5MM
C1, C3: 100nF; 0805-CAP
D1: 1N4148; SOD123-2.7X1.6
GROVE_I2C: 4P-2.0; HW4-2.0
I2C_OLED: CON_HEADER_1X04'NO_LOCK'; 1X04_NO_LOCK
J$2: ANTENNATINY; SMA_UFL_PAD_TINY
JP2: RXLED; PAD-JUMPER-2-NC_BY_TRACE_YES_SILK
JP3: JUMPER-PAD-2-NC_BY_TRACE; PAD-JUMPER-2-NC_BY_TRACE_YES_SILK
R1, R2: 4.7K; 0805-RES
U1: 24AA02E64T; SOT95P270X145-5N
U$1: LOLIN32 LITE; LOLIN32_LITE
U$2, U$3: PAD-JUMPER-SWAPSWAP; PAD-JUMPER-SWAP
U$6: RA02 433MHZ; LORA-RA2-SMD
WS2812: WS2812B

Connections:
3V3: C1.1, GROVE_I2C.3, JP2.2, R1.2, R2.2, U1.4 (VCC), U$1.3V3@2 (3V3), U$2.4, U$2.44 (4), U$6.3 (3.3V)
5V: D1.1, JP3.2
ANT: J$2.ANT1 (SIGNAL), J$2.ANT2 (SIGNAL), J$2.ANT3 (SIGNAL), U$6.1 (ANT)
DO: WS2812.2 (DOUT)
GND: BTN.2 (A1), C1.2, C3.2, GROVE_I2C.4, J$2.GND1 (GND), J$2.GND2 (GND), J$2.GND3 (GND), J$2.GND4 (GND), U1.2 (VSS), U$1.GND@1 (GND), U$2.1, U$2.11 (1), U$6.2 (GND.2), U$6.9 (GND.3), U$6.16 (GND.4), WS2812.3 (GND)
IO4: U$1.4, U$6.7 (DIO2)
IO5: U$1.5, U$6.15 (NSS)
IO13: U$1.13, WS2812.4 (DIN)
IO15: BTN.3 (B0), U$1.15
IO18: U$1.18, U$6.12 (SCK)
IO19: U$1.19, U$6.13 (MISO)
IO23: U$1.23, U$6.14 (MOSI)
IO25: U$1.25, U$6.4 (RESET)
IO26: U$1.26, U$6.6 (DIO1)
IO27: U$1.27, U$6.5 (DIO0)
unnamed: I2C_OLED.1, U$2.3
unnamed: I2C_OLED.2, U$2.2
unnamed: I2C_OLED.3, U$3.2
unnamed: I2C_OLED.4, U$3.3
SCL: GROVE_I2C.1, R2.1, U1.1 (SCL), U$1.12, U$3.1, U$3.11 (1)
SDA: GROVE_I2C.2, R1.1, U1.3 (SDA), U$1.14, U$3.4, U$3.44 (4)
VLED: C3.1, D1.2, JP2.1, JP3.1, WS2812.1 (VDD)

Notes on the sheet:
File:
WeMos LoLin32 Lite Headers
433MHz
Need to activate ESP32 pullup on GPIO15
SCK
MOSI
MISO
LEd
LoLin32 has no 5V pinout so leave PAD JP3 to solder wire if needed (and cut JP2)
3.3V could work for LED

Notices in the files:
parts and their libraries:
microbuilder: This work is placed in the public domain, and may be freely used for commercial and non-commercial work with the following conditions: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
SparkFun-Connectors: Licensing: Creative Commons ShareAlike 4.0 International - https://creativecommons.org/licenses/by-sa/4.0
